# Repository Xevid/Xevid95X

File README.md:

# Xevid95X
 Xevid95X Keyboard for Junior Project

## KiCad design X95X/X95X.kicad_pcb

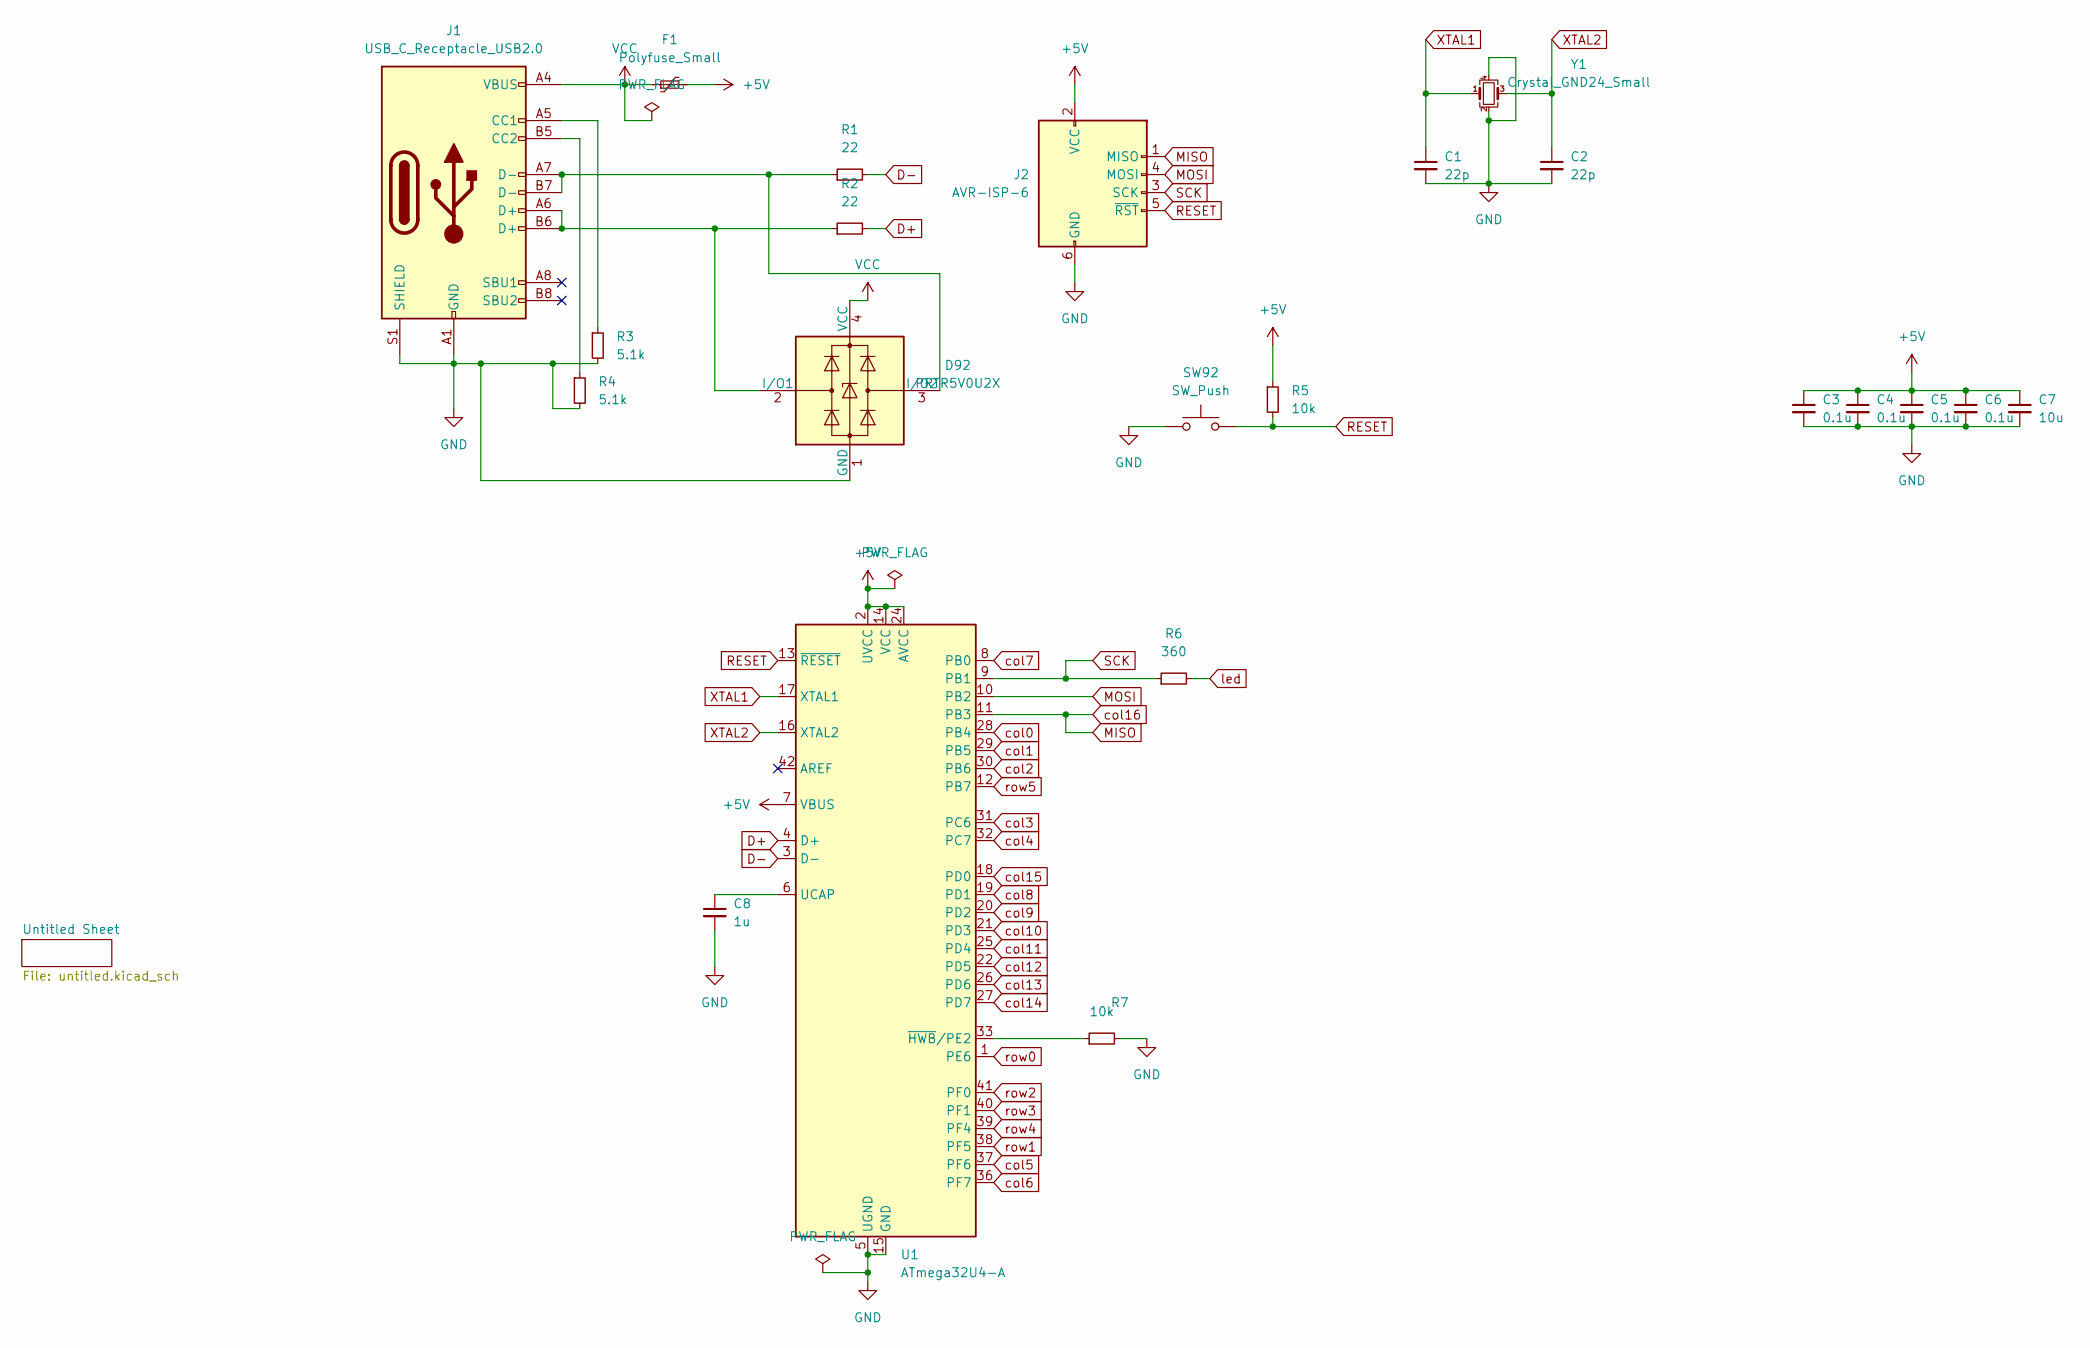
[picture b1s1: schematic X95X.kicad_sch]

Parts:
C1, C2: 22p; C_0805_2012Metric_Pad1.18x1.45mm_HandSolder
C3, C4, C5, C6: 0.1u; C_0805_2012Metric_Pad1.18x1.45mm_HandSolder
C7: 10u; C_0805_2012Metric_Pad1.18x1.45mm_HandSolder
C8: 1u; C_0805_2012Metric_Pad1.18x1.45mm_HandSolder
D92: PRTR5V0U2X; SOT143B
F1: Polyfuse_Small; Fuse_1206_3216Metric_Pad1.42x1.75mm_HandSolder
J1: USB_C_Receptacle_USB2.0; USB_C_Receptacle_HRO_TYPE-C-31-M-14
J2: AVR-ISP-6; Reset_Pretty-Mask
R1, R2: 22; R_0805_2012Metric_Pad1.20x1.40mm_HandSolder
R3, R4: 5.1k; R_0805_2012Metric_Pad1.20x1.40mm_HandSolder
R5, R7: 10k; R_0805_2012Metric_Pad1.20x1.40mm_HandSolder
R6: 360; R_0805_2012Metric_Pad1.20x1.40mm_HandSolder
SW92: SW_Push; SW_SPST_SKQG_WithStem
U1: ATmega32U4-A; TQFP-44_10x10mm_P0.8mm
Y1: Crystal_GND24_Small; Crystal_SMD_3225-4Pin_3.2x2.5mm_HandSoldering

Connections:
+5V: C3.1, C4.1, C5.1, C6.1, C7.1, F1.2, J2.2 (VCC), R5.1, U1.2 (UVCC), U1.7 (VBUS), U1.14 (VCC), U1.24 (AVCC), U1.34 (VCC), U1.44 (AVCC)
D+: R2.2, U1.4 (D+)
D-: R1.2, U1.3 (D-)
GND: C1.2, C2.2, C3.2, C4.2, C5.2, C6.2, C7.2, C8.2, D92.1 (GND), J1.A1 (GND), J1.A12 (GND), J1.B1 (GND), J1.B12 (GND), J1.S1 (SHIELD), J2.6 (GND), R3.2, R4.2, R7.2, SW92.1, U1.5 (UGND), U1.15 (GND), U1.23 (GND), U1.35 (GND), U1.43 (GND), Y1.2, Y1.4; also elsewhere on the board
MISO: J2.1 (MISO), U1.11 (PB3); also elsewhere on the board
MOSI: J2.4 (MOSI), U1.10 (PB2)
unnamed: C8.1, U1.6 (UCAP)
unnamed: D92.2 (I/O1), J1.A6 (D+), J1.B6 (D+), R2.1
unnamed: D92.3 (I/O2), J1.A7 (D-), J1.B7 (D-), R1.1
unnamed: J1.A5 (CC1), R3.1
unnamed: J1.B5 (CC2), R4.1
unnamed: R7.1, U1.33 (~HWB/PE2)
RESET: J2.5 (~RST), R5.2, SW92.2, U1.13 (~RESET)
SCK: J2.3 (SCK), R6.1, U1.9 (PB1)
VCC: D92.4 (VCC), F1.1, J1.A4 (VBUS), J1.A9 (VBUS), J1.B4 (VBUS), J1.B9 (VBUS); also elsewhere on the board
XTAL1: C1.1, U1.17 (XTAL1), Y1.1
XTAL2: C2.1, U1.16 (XTAL2), Y1.3
col0: U1.28 (PB4); also elsewhere on the board
col1: U1.29 (PB5); also elsewhere on the board
col2: U1.30 (PB6); also elsewhere on the board
col3: U1.31 (PC6); also elsewhere on the board
col4: U1.32 (PC7); also elsewhere on the board
col5: U1.37 (PF6); also elsewhere on the board
col6: U1.36 (PF7); also elsewhere on the board
col7: U1.8 (PB0); also elsewhere on the board
col8: U1.19 (PD1); also elsewhere on the board
col9: U1.20 (PD2); also elsewhere on the board
col10: U1.21 (PD3); also elsewhere on the board
col11: U1.25 (PD4); also elsewhere on the board
col12: U1.22 (PD5); also elsewhere on the board
col13: U1.26 (PD6); also elsewhere on the board
col14: U1.27 (PD7); also elsewhere on the board
col15: U1.18 (PD0); also elsewhere on the board
led: R6.2; also elsewhere on the board
row0: U1.1 (PE6); also elsewhere on the board
row1: U1.38 (PF5); also elsewhere on the board
row2: U1.41 (PF0); also elsewhere on the board
row3: U1.40 (PF1); also elsewhere on the board
row4: U1.39 (PF4); also elsewhere on the board
row5: U1.12 (PB7); also elsewhere on the board

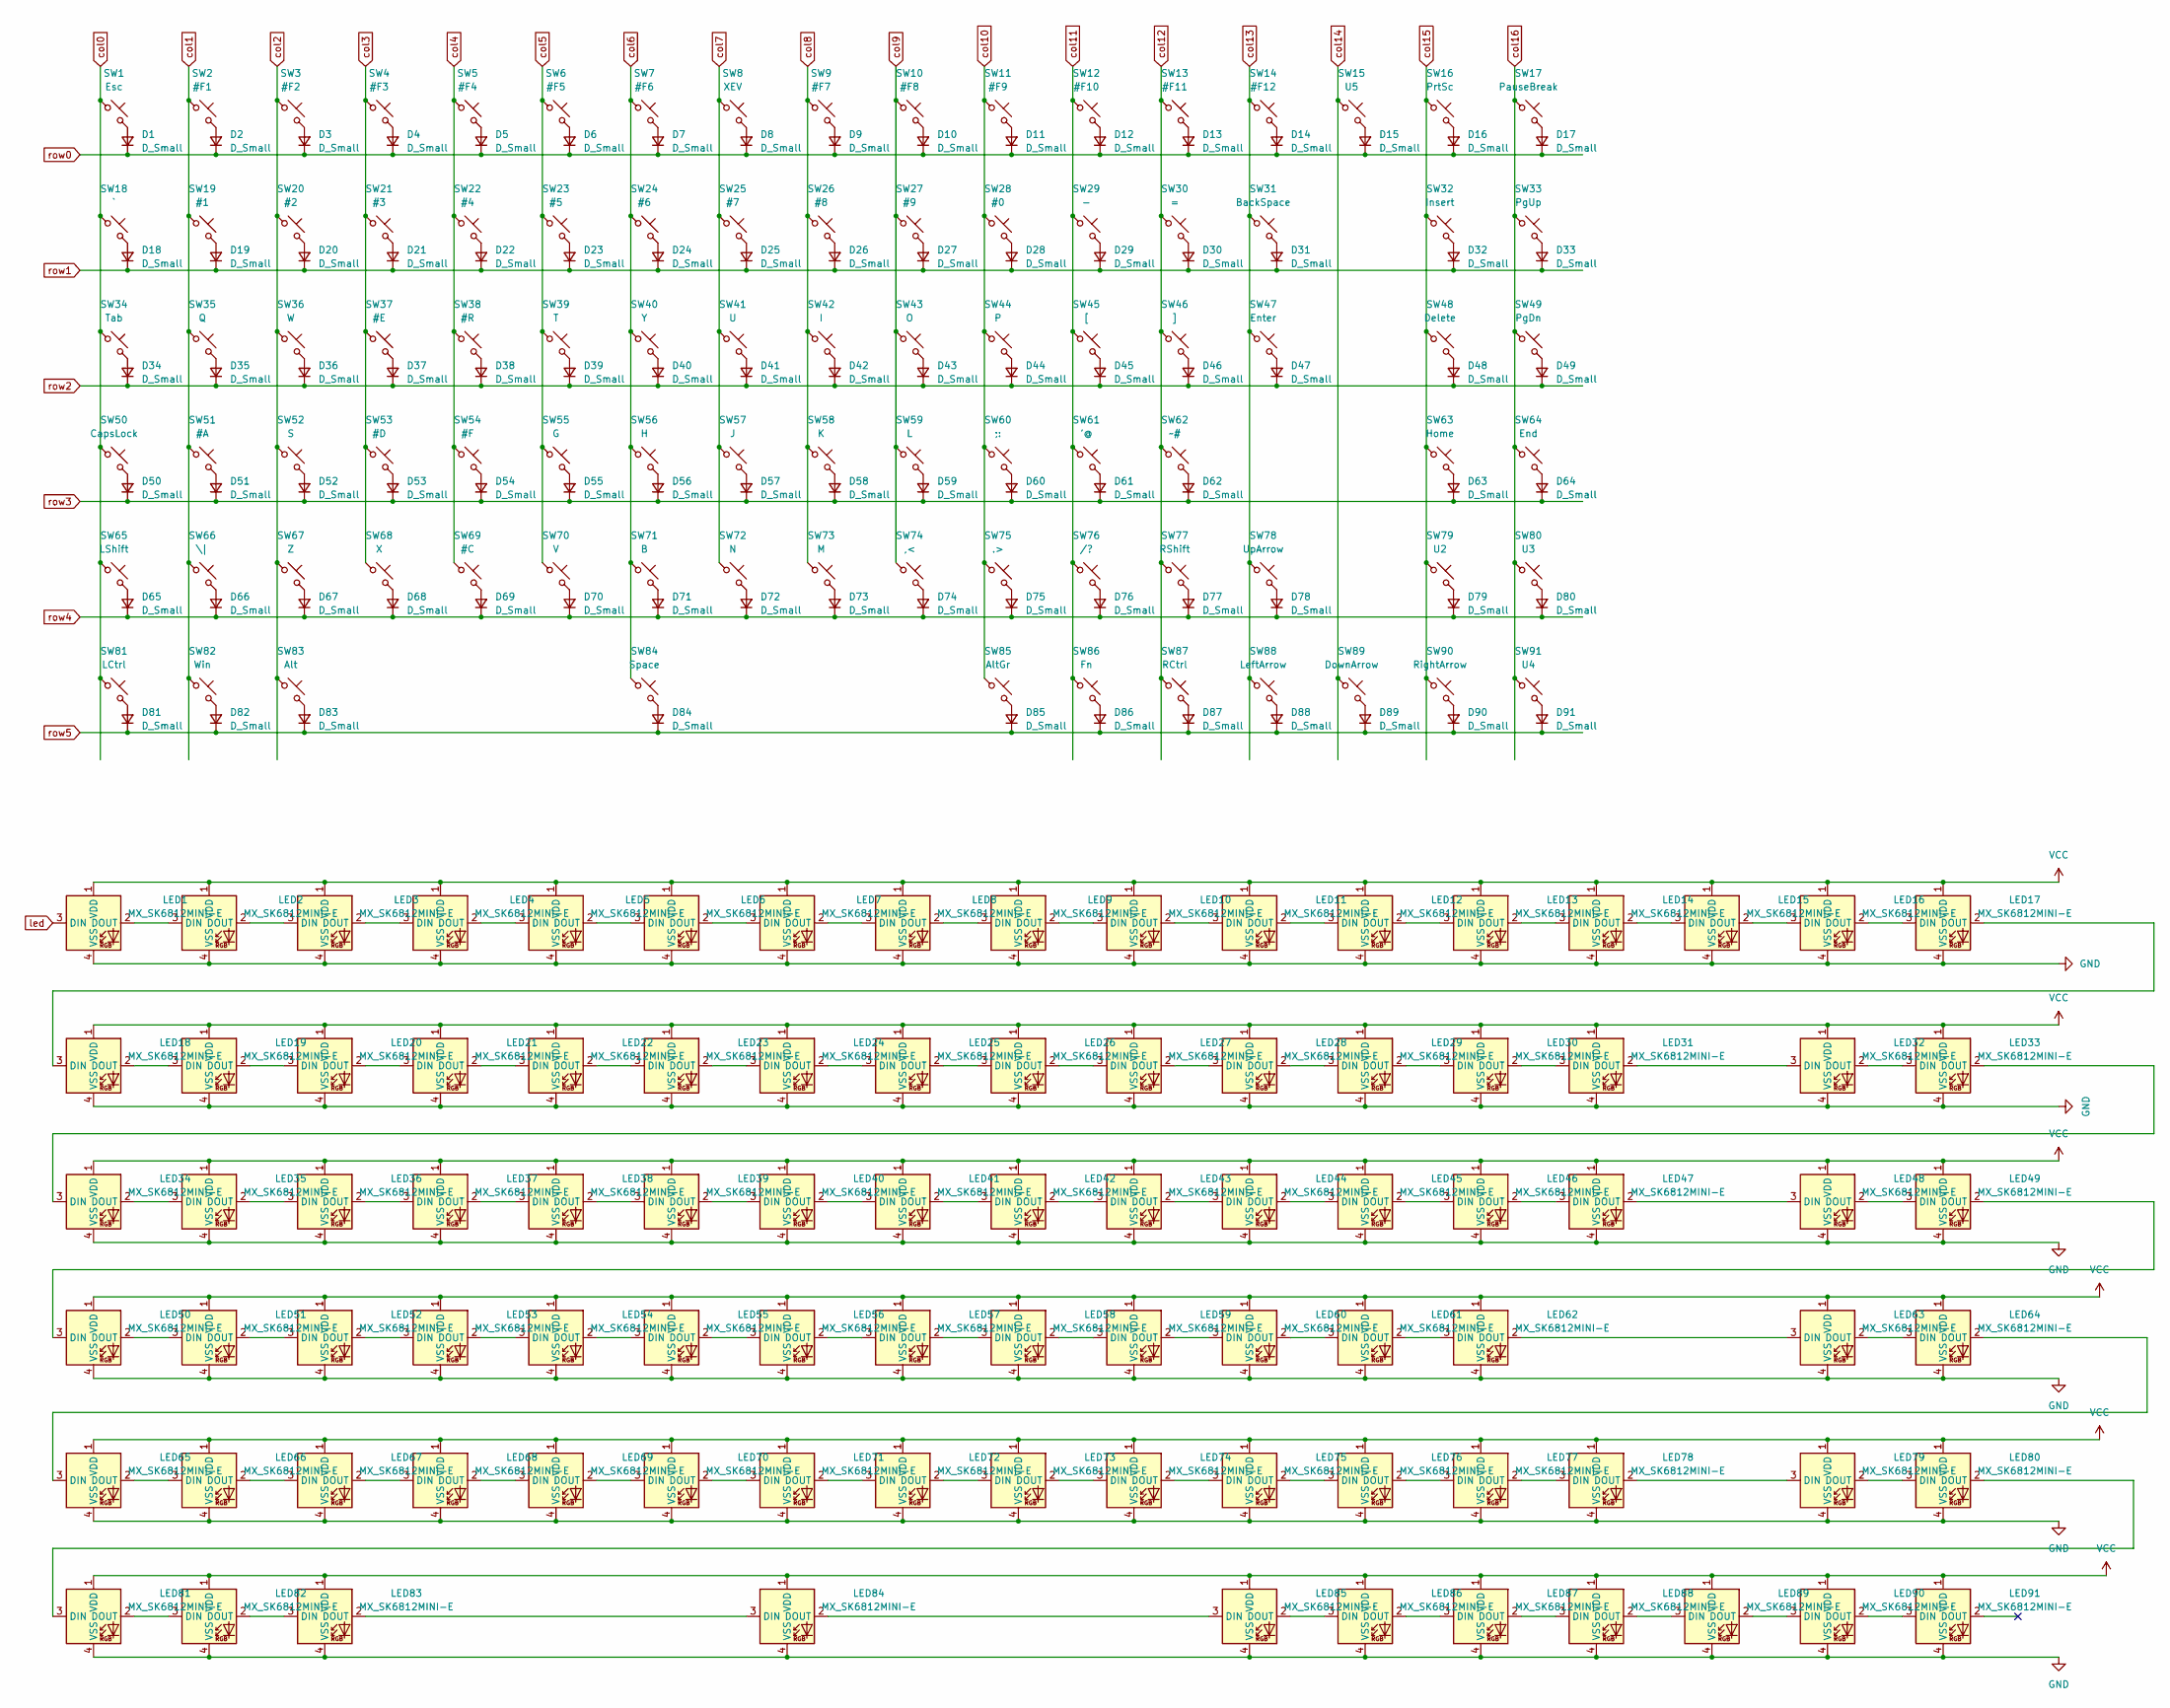
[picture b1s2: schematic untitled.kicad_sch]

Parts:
D1, D2, D3, D4, D5, D6, D7, D8, D9, D10, D11, D12, D13, D14, D15, D16, D17, D18, D19, D20, D21, D22, D23, D24, D25, D26, D27, D28, D29, D30, D31, D32, D33, D34, D35, D36, D37, D38, D39, D40, D41, D42, D43, D44, D45, D46, D47, D48, D49, D50, D51, D52, D53, D54, D55, D56, D57, D58, D59, D60, D61, D62, D63, D64, D65, D66, D67, D68, D69, D70, D71, D72, D73, D74, D75, D76, D77, D78, D79, D80, D81, D82, D83, D84, D85, D86, D87, D88, D89, D90, D91: D_Small; D_SOD-123
LED1, LED2, LED3, LED4, LED5, LED6, LED7, LED8, LED9, LED10, LED11, LED12, LED13, LED14, LED15, LED16, LED17, LED18, LED19, LED20, LED21, LED22, LED23, LED24, LED25, LED26, LED27, LED28, LED29, LED30, LED31, LED32, LED33, LED34, LED35, LED36, LED37, LED38, LED39, LED40, LED41, LED42, LED43, LED44, LED45, LED46, LED47, LED48, LED49, LED50, LED51, LED52, LED53, LED54, LED55, LED56, LED57, LED58, LED59, LED60, LED61, LED62, LED63, LED64, LED65, LED66, LED67, LED68, LED69, LED70, LED71, LED72, LED73, LED74, LED75, LED76, LED77, LED78, LED79, LED80, LED81, LED82, LED83, LED84, LED85, LED86, LED87, LED88, LED89, LED90, LED91: MX_SK6812MINI-E; LED_MX_6028R
SW1: Esc; SW_MX_1u
SW2: #F1; SW_MX_1u
SW3: #F2; SW_MX_1u
SW4: #F3; SW_MX_1u
SW5: #F4; SW_MX_1u
SW6: #F5; SW_MX_1u
SW7: #F6; SW_MX_1u
SW8: XEV; SW_MX_1u
SW9: #F7; SW_MX_1u
SW10: #F8; SW_MX_1u
SW11: #F9; SW_MX_1u
SW12: #F10; SW_MX_1u
SW13: #F11; SW_MX_1u
SW14: #F12; SW_MX_1u
SW15: U5; SW_MX_1u
SW16: PrtSc; SW_MX_1u
SW17: PauseBreak; SW_MX_1u
SW18: `; SW_MX_1u
SW19: #1; SW_MX_1u
SW20: #2; SW_MX_1u
SW21: #3; SW_MX_1u
SW22: #4; SW_MX_1u
SW23: #5; SW_MX_1u
SW24: #6; SW_MX_1u
SW25: #7; SW_MX_1u
SW26: #8; SW_MX_1u
SW27: #9; SW_MX_1u
SW28: #0; SW_MX_1u
SW29: -; SW_MX_1u
SW30: =; SW_MX_1u
SW31: BackSpace; SW_MX_1u
SW32: Insert; SW_MX_1u
SW33: PgUp; SW_MX_1u
SW34: Tab; SW_MX_1.5u
SW35: Q; SW_MX_1u
SW36: W; SW_MX_1u
SW37: #E; SW_MX_1u
SW38: #R; SW_MX_1u
SW39: T; SW_MX_1u
SW40: Y; SW_MX_1u
SW41: U; SW_MX_1u
SW42: I; SW_MX_1u
SW43: O; SW_MX_1u
SW44: P; SW_MX_1u
SW45: [; SW_MX_1u
SW46: ]; SW_MX_1u
SW47: Enter; SW_MX_1u
SW48: Delete; SW_MX_1u
SW49: PgDn; SW_MX_1u
SW50: CapsLock; SW_MX_1.75u
SW51: #A; SW_MX_1u
SW52: S; SW_MX_1u
SW53: #D; SW_MX_1u
SW54: #F; SW_MX_1u
SW55: G; SW_MX_1u
SW56: H; SW_MX_1u
SW57: J; SW_MX_1u
SW58: K; SW_MX_1u
SW59: L; SW_MX_1u
SW60: ;:; SW_MX_1u
SW61: '@; SW_MX_1u
SW62: ~#; SW_MX_1u
SW63: Home; SW_MX_1u
SW64: End; SW_MX_1u
SW65: LShift; SW_MX_1.25u
SW66: \|; SW_MX_1u
SW67: Z; SW_MX_1u
SW68: X; SW_MX_1u
SW69: #C; SW_MX_1u
SW70: V; SW_MX_1u
SW71: B; SW_MX_1u
SW72: N; SW_MX_1u
SW73: M; SW_MX_1u
SW74: ,<; SW_MX_1u
SW75: .>; SW_MX_1u
SW76: /?; SW_MX_1u
SW77: RShift; SW_MX_1.75u
SW78: UpArrow; SW_MX_1u
SW79: U2; SW_MX_1u
SW80: U3; SW_MX_1u
SW81: LCtrl; SW_MX_1.25u
SW82: Win; SW_MX_1.25u
SW83: Alt; SW_MX_1.25u
SW84: Space; SW_MX_1u
SW85: AltGr; SW_MX_1u
SW86: Fn; SW_MX_1u
SW87: RCtrl; SW_MX_1u
SW88: LeftArrow; SW_MX_1u
SW89: DownArrow; SW_MX_1u
SW90: RightArrow; SW_MX_1u
SW91: U4; SW_MX_1u

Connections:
GND: LED1.4 (VSS), LED2.4 (VSS), LED3.4 (VSS), LED4.4 (VSS), LED5.4 (VSS), LED6.4 (VSS), LED7.4 (VSS), LED8.4 (VSS), LED9.4 (VSS), LED10.4 (VSS), LED11.4 (VSS), LED12.4 (VSS), LED13.4 (VSS), LED14.4 (VSS), LED15.4 (VSS), LED16.4 (VSS), LED17.4 (VSS), LED18.4 (VSS), LED19.4 (VSS), LED20.4 (VSS), LED21.4 (VSS), LED22.4 (VSS), LED23.4 (VSS), LED24.4 (VSS), LED25.4 (VSS), LED26.4 (VSS), LED27.4 (VSS), LED28.4 (VSS), LED29.4 (VSS), LED30.4 (VSS), LED31.4 (VSS), LED32.4 (VSS), LED33.4 (VSS), LED34.4 (VSS), LED35.4 (VSS), LED36.4 (VSS), LED37.4 (VSS), LED38.4 (VSS), LED39.4 (VSS), LED40.4 (VSS), LED41.4 (VSS), LED42.4 (VSS), LED43.4 (VSS), LED44.4 (VSS), LED45.4 (VSS), LED46.4 (VSS), LED47.4 (VSS), LED48.4 (VSS), LED49.4 (VSS), LED50.4 (VSS), LED51.4 (VSS), LED52.4 (VSS), LED53.4 (VSS), LED54.4 (VSS), LED55.4 (VSS), LED56.4 (VSS), LED57.4 (VSS), LED58.4 (VSS), LED59.4 (VSS), LED60.4 (VSS), LED61.4 (VSS), LED62.4 (VSS), LED63.4 (VSS), LED64.4 (VSS), LED65.4 (VSS), LED66.4 (VSS), LED67.4 (VSS), LED68.4 (VSS), LED69.4 (VSS), LED70.4 (VSS), LED71.4 (VSS), LED72.4 (VSS), LED73.4 (VSS), LED74.4 (VSS), LED75.4 (VSS), LED76.4 (VSS), LED77.4 (VSS), LED78.4 (VSS), LED79.4 (VSS), LED80.4 (VSS), LED81.4 (VSS), LED82.4 (VSS), LED83.4 (VSS), LED84.4 (VSS), LED85.4 (VSS), LED86.4 (VSS), LED87.4 (VSS), LED88.4 (VSS), LED89.4 (VSS), LED90.4 (VSS), LED91.4 (VSS); also elsewhere on the board
MISO: SW17.1, SW33.1, SW49.1, SW64.1, SW80.1, SW91.1; also elsewhere on the board
unnamed: D1.2 (A), SW1.2
unnamed: D2.2 (A), SW2.2
unnamed: D3.2 (A), SW3.2
unnamed: D4.2 (A), SW4.2
unnamed: D5.2 (A), SW5.2
unnamed: D6.2 (A), SW6.2
unnamed: D7.2 (A), SW7.2
unnamed: D8.2 (A), SW8.2
unnamed: D9.2 (A), SW9.2
unnamed: D10.2 (A), SW10.2
unnamed: D11.2 (A), SW11.2
unnamed: D12.2 (A), SW12.2
unnamed: D13.2 (A), SW13.2
unnamed: D14.2 (A), SW14.2
unnamed: D15.2 (A), SW15.2
unnamed: D16.2 (A), SW16.2
unnamed: D17.2 (A), SW17.2
unnamed: D18.2 (A), SW18.2
unnamed: D19.2 (A), SW19.2
unnamed: D20.2 (A), SW20.2
unnamed: D21.2 (A), SW21.2
unnamed: D22.2 (A), SW22.2
unnamed: D23.2 (A), SW23.2
unnamed: D24.2 (A), SW24.2
unnamed: D25.2 (A), SW25.2
unnamed: D26.2 (A), SW26.2
unnamed: D27.2 (A), SW27.2
unnamed: D28.2 (A), SW28.2
unnamed: D29.2 (A), SW29.2
unnamed: D30.2 (A), SW30.2
unnamed: D31.2 (A), SW31.2
unnamed: D32.2 (A), SW32.2
unnamed: D33.2 (A), SW33.2
unnamed: D34.2 (A), SW34.2
unnamed: D35.2 (A), SW35.2
unnamed: D36.2 (A), SW36.2
unnamed: D37.2 (A), SW37.2
unnamed: D38.2 (A), SW38.2
unnamed: D39.2 (A), SW39.2
unnamed: D40.2 (A), SW40.2
unnamed: D41.2 (A), SW41.2
unnamed: D42.2 (A), SW42.2
unnamed: D43.2 (A), SW43.2
unnamed: D44.2 (A), SW44.2
unnamed: D45.2 (A), SW45.2
unnamed: D46.2 (A), SW46.2
unnamed: D47.2 (A), SW47.2
unnamed: D48.2 (A), SW48.2
unnamed: D49.2 (A), SW49.2
unnamed: D50.2 (A), SW50.2
unnamed: D51.2 (A), SW51.2
unnamed: D52.2 (A), SW52.2
unnamed: D53.2 (A), SW53.2
unnamed: D54.2 (A), SW54.2
unnamed: D55.2 (A), SW55.2
unnamed: D56.2 (A), SW56.2
unnamed: D57.2 (A), SW57.2
unnamed: D58.2 (A), SW58.2
unnamed: D59.2 (A), SW59.2
unnamed: D60.2 (A), SW60.2
unnamed: D61.2 (A), SW61.2
unnamed: D62.2 (A), SW62.2
unnamed: D63.2 (A), SW63.2
unnamed: D64.2 (A), SW64.2
unnamed: D65.2 (A), SW65.2
unnamed: D66.2 (A), SW66.2
unnamed: D67.2 (A), SW67.2
unnamed: D68.2 (A), SW68.2
unnamed: D69.2 (A), SW69.2
unnamed: D70.2 (A), SW70.2
unnamed: D71.2 (A), SW71.2
unnamed: D72.2 (A), SW72.2
unnamed: D73.2 (A), SW73.2
unnamed: D74.2 (A), SW74.2
unnamed: D75.2 (A), SW75.2
unnamed: D76.2 (A), SW76.2
unnamed: D77.2 (A), SW77.2
unnamed: D78.2 (A), SW78.2
unnamed: D79.2 (A), SW79.2
unnamed: D80.2 (A), SW80.2
unnamed: D81.2 (A), SW81.2
unnamed: D82.2 (A), SW82.2
unnamed: D83.2 (A), SW83.2
unnamed: D84.2 (A), SW84.2
unnamed: D85.2 (A), SW85.2
unnamed: D86.2 (A), SW86.2
unnamed: D87.2 (A), SW87.2
unnamed: D88.2 (A), SW88.2
unnamed: D89.2 (A), SW89.2
unnamed: D90.2 (A), SW90.2
unnamed: D91.2 (A), SW91.2
unnamed: LED1.2 (DOUT), LED2.3 (DIN)
unnamed: LED2.2 (DOUT), LED3.3 (DIN)
unnamed: LED3.2 (DOUT), LED4.3 (DIN)
unnamed: LED4.2 (DOUT), LED5.3 (DIN)
unnamed: LED5.2 (DOUT), LED6.3 (DIN)
unnamed: LED6.2 (DOUT), LED7.3 (DIN)
unnamed: LED7.2 (DOUT), LED8.3 (DIN)
unnamed: LED8.2 (DOUT), LED9.3 (DIN)
unnamed: LED10.2 (DOUT), LED11.3 (DIN)
unnamed: LED9.2 (DOUT), LED10.3 (DIN)
unnamed: LED11.2 (DOUT), LED12.3 (DIN)
unnamed: LED12.2 (DOUT), LED13.3 (DIN)
unnamed: LED13.2 (DOUT), LED14.3 (DIN)
unnamed: LED14.2 (DOUT), LED15.3 (DIN)
unnamed: LED15.2 (DOUT), LED16.3 (DIN)
unnamed: LED16.2 (DOUT), LED17.3 (DIN)
unnamed: LED17.2 (DOUT), LED18.3 (DIN)
unnamed: LED18.2 (DOUT), LED19.3 (DIN)
unnamed: LED19.2 (DOUT), LED20.3 (DIN)
unnamed: LED20.2 (DOUT), LED21.3 (DIN)
unnamed: LED21.2 (DOUT), LED22.3 (DIN)
unnamed: LED22.2 (DOUT), LED23.3 (DIN)
unnamed: LED23.2 (DOUT), LED24.3 (DIN)
unnamed: LED24.2 (DOUT), LED25.3 (DIN)
unnamed: LED25.2 (DOUT), LED26.3 (DIN)
unnamed: LED26.2 (DOUT), LED27.3 (DIN)
unnamed: LED27.2 (DOUT), LED28.3 (DIN)
unnamed: LED28.2 (DOUT), LED29.3 (DIN)
unnamed: LED29.2 (DOUT), LED30.3 (DIN)
unnamed: LED30.2 (DOUT), LED31.3 (DIN)
unnamed: LED32.2 (DOUT), LED33.3 (DIN)
unnamed: LED31.2 (DOUT), LED32.3 (DIN)
unnamed: LED33.2 (DOUT), LED34.3 (DIN)
unnamed: LED34.2 (DOUT), LED35.3 (DIN)
unnamed: LED35.2 (DOUT), LED36.3 (DIN)
unnamed: LED36.2 (DOUT), LED37.3 (DIN)
unnamed: LED37.2 (DOUT), LED38.3 (DIN)
unnamed: LED38.2 (DOUT), LED39.3 (DIN)
unnamed: LED39.2 (DOUT), LED40.3 (DIN)
unnamed: LED40.2 (DOUT), LED41.3 (DIN)
unnamed: LED41.2 (DOUT), LED42.3 (DIN)
unnamed: LED42.2 (DOUT), LED43.3 (DIN)
unnamed: LED43.2 (DOUT), LED44.3 (DIN)
unnamed: LED44.2 (DOUT), LED45.3 (DIN)
unnamed: LED45.2 (DOUT), LED46.3 (DIN)
unnamed: LED46.2 (DOUT), LED47.3 (DIN)
unnamed: LED48.2 (DOUT), LED49.3 (DIN)
unnamed: LED47.2 (DOUT), LED48.3 (DIN)
unnamed: LED49.2 (DOUT), LED50.3 (DIN)
unnamed: LED50.2 (DOUT), LED51.3 (DIN)
unnamed: LED51.2 (DOUT), LED52.3 (DIN)
unnamed: LED52.2 (DOUT), LED53.3 (DIN)
unnamed: LED53.2 (DOUT), LED54.3 (DIN)
unnamed: LED54.2 (DOUT), LED55.3 (DIN)
unnamed: LED55.2 (DOUT), LED56.3 (DIN)
unnamed: LED56.2 (DOUT), LED57.3 (DIN)
unnamed: LED57.2 (DOUT), LED58.3 (DIN)
unnamed: LED58.2 (DOUT), LED59.3 (DIN)
unnamed: LED59.2 (DOUT), LED60.3 (DIN)
unnamed: LED60.2 (DOUT), LED61.3 (DIN)
unnamed: LED61.2 (DOUT), LED62.3 (DIN)
unnamed: LED62.2 (DOUT), LED63.3 (DIN)
unnamed: LED63.2 (DOUT), LED64.3 (DIN)
unnamed: LED64.2 (DOUT), LED65.3 (DIN)
unnamed: LED65.2 (DOUT), LED66.3 (DIN)
unnamed: LED66.2 (DOUT), LED67.3 (DIN)
unnamed: LED67.2 (DOUT), LED68.3 (DIN)
unnamed: LED68.2 (DOUT), LED69.3 (DIN)
unnamed: LED69.2 (DOUT), LED70.3 (DIN)
unnamed: LED70.2 (DOUT), LED71.3 (DIN)
unnamed: LED71.2 (DOUT), LED72.3 (DIN)
unnamed: LED72.2 (DOUT), LED73.3 (DIN)
unnamed: LED73.2 (DOUT), LED74.3 (DIN)
unnamed: LED74.2 (DOUT), LED75.3 (DIN)
unnamed: LED75.2 (DOUT), LED76.3 (DIN)
unnamed: LED76.2 (DOUT), LED77.3 (DIN)
unnamed: LED77.2 (DOUT), LED78.3 (DIN)
unnamed: LED78.2 (DOUT), LED79.3 (DIN)
unnamed: LED79.2 (DOUT), LED80.3 (DIN)
unnamed: LED80.2 (DOUT), LED81.3 (DIN)
unnamed: LED81.2 (DOUT), LED82.3 (DIN)
unnamed: LED82.2 (DOUT), LED83.3 (DIN)
unnamed: LED83.2 (DOUT), LED84.3 (DIN)
unnamed: LED84.2 (DOUT), LED85.3 (DIN)
unnamed: LED86.2 (DOUT), LED87.3 (DIN)
unnamed: LED85.2 (DOUT), LED86.3 (DIN)
unnamed: LED87.2 (DOUT), LED88.3 (DIN)
unnamed: LED89.2 (DOUT), LED90.3 (DIN)
unnamed: LED88.2 (DOUT), LED89.3 (DIN)
unnamed: LED90.2 (DOUT), LED91.3 (DIN)
VCC: LED1.1 (VDD), LED2.1 (VDD), LED3.1 (VDD), LED4.1 (VDD), LED5.1 (VDD), LED6.1 (VDD), LED7.1 (VDD), LED8.1 (VDD), LED9.1 (VDD), LED10.1 (VDD), LED11.1 (VDD), LED12.1 (VDD), LED13.1 (VDD), LED14.1 (VDD), LED15.1 (VDD), LED16.1 (VDD), LED17.1 (VDD), LED18.1 (VDD), LED19.1 (VDD), LED20.1 (VDD), LED21.1 (VDD), LED22.1 (VDD), LED23.1 (VDD), LED24.1 (VDD), LED25.1 (VDD), LED26.1 (VDD), LED27.1 (VDD), LED28.1 (VDD), LED29.1 (VDD), LED30.1 (VDD), LED31.1 (VDD), LED32.1 (VDD), LED33.1 (VDD), LED34.1 (VDD), LED35.1 (VDD), LED36.1 (VDD), LED37.1 (VDD), LED38.1 (VDD), LED39.1 (VDD), LED40.1 (VDD), LED41.1 (VDD), LED42.1 (VDD), LED43.1 (VDD), LED44.1 (VDD), LED45.1 (VDD), LED46.1 (VDD), LED47.1 (VDD), LED48.1 (VDD), LED49.1 (VDD), LED50.1 (VDD), LED51.1 (VDD), LED52.1 (VDD), LED53.1 (VDD), LED54.1 (VDD), LED55.1 (VDD), LED56.1 (VDD), LED57.1 (VDD), LED58.1 (VDD), LED59.1 (VDD), LED60.1 (VDD), LED61.1 (VDD), LED62.1 (VDD), LED63.1 (VDD), LED64.1 (VDD), LED65.1 (VDD), LED66.1 (VDD), LED67.1 (VDD), LED68.1 (VDD), LED69.1 (VDD), LED70.1 (VDD), LED71.1 (VDD), LED72.1 (VDD), LED73.1 (VDD), LED74.1 (VDD), LED75.1 (VDD), LED76.1 (VDD), LED77.1 (VDD), LED78.1 (VDD), LED79.1 (VDD), LED80.1 (VDD), LED81.1 (VDD), LED82.1 (VDD), LED83.1 (VDD), LED84.1 (VDD), LED85.1 (VDD), LED86.1 (VDD), LED87.1 (VDD), LED88.1 (VDD), LED89.1 (VDD), LED90.1 (VDD), LED91.1 (VDD); also elsewhere on the board
col0: SW1.1, SW18.1, SW34.1, SW50.1, SW65.1, SW81.1; also elsewhere on the board
col1: SW2.1, SW19.1, SW35.1, SW51.1, SW66.1, SW82.1; also elsewhere on the board
col2: SW3.1, SW20.1, SW36.1, SW52.1, SW67.1, SW83.1; also elsewhere on the board
col3: SW4.1, SW21.1, SW37.1, SW53.1, SW68.1; also elsewhere on the board
col4: SW5.1, SW22.1, SW38.1, SW54.1, SW69.1; also elsewhere on the board
col5: SW6.1, SW23.1, SW39.1, SW55.1, SW70.1; also elsewhere on the board
col6: SW7.1, SW24.1, SW40.1, SW56.1, SW71.1, SW84.1; also elsewhere on the board
col7: SW8.1, SW25.1, SW41.1, SW57.1, SW72.1; also elsewhere on the board
col8: SW9.1, SW26.1, SW42.1, SW58.1, SW73.1; also elsewhere on the board
col9: SW10.1, SW27.1, SW43.1, SW59.1, SW74.1; also elsewhere on the board
col10: SW11.1, SW28.1, SW44.1, SW60.1, SW75.1, SW85.1; also elsewhere on the board
col11: SW12.1, SW29.1, SW45.1, SW61.1, SW76.1, SW86.1; also elsewhere on the board
col12: SW13.1, SW30.1, SW46.1, SW62.1, SW77.1, SW87.1; also elsewhere on the board
col13: SW14.1, SW31.1, SW47.1, SW78.1, SW88.1; also elsewhere on the board
col14: SW15.1, SW89.1; also elsewhere on the board
col15: SW16.1, SW32.1, SW48.1, SW63.1, SW79.1, SW90.1; also elsewhere on the board
led: LED1.3 (DIN); also elsewhere on the board
row0: D1.1 (K), D2.1 (K), D3.1 (K), D4.1 (K), D5.1 (K), D6.1 (K), D7.1 (K), D8.1 (K), D9.1 (K), D10.1 (K), D11.1 (K), D12.1 (K), D13.1 (K), D14.1 (K), D15.1 (K), D16.1 (K), D17.1 (K); also elsewhere on the board
row1: D18.1 (K), D19.1 (K), D20.1 (K), D21.1 (K), D22.1 (K), D23.1 (K), D24.1 (K), D25.1 (K), D26.1 (K), D27.1 (K), D28.1 (K), D29.1 (K), D30.1 (K), D31.1 (K), D32.1 (K), D33.1 (K); also elsewhere on the board
row2: D34.1 (K), D35.1 (K), D36.1 (K), D37.1 (K), D38.1 (K), D39.1 (K), D40.1 (K), D41.1 (K), D42.1 (K), D43.1 (K), D44.1 (K), D45.1 (K), D46.1 (K), D47.1 (K), D48.1 (K), D49.1 (K); also elsewhere on the board
row3: D50.1 (K), D51.1 (K), D52.1 (K), D53.1 (K), D54.1 (K), D55.1 (K), D56.1 (K), D57.1 (K), D58.1 (K), D59.1 (K), D60.1 (K), D61.1 (K), D62.1 (K), D63.1 (K), D64.1 (K); also elsewhere on the board
row4: D65.1 (K), D66.1 (K), D67.1 (K), D68.1 (K), D69.1 (K), D70.1 (K), D71.1 (K), D72.1 (K), D73.1 (K), D74.1 (K), D75.1 (K), D76.1 (K), D77.1 (K), D78.1 (K), D79.1 (K), D80.1 (K); also elsewhere on the board
row5: D81.1 (K), D82.1 (K), D83.1 (K), D84.1 (K), D85.1 (K), D86.1 (K), D87.1 (K), D88.1 (K), D89.1 (K), D90.1 (K), D91.1 (K); also elsewhere on the board

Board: 2 copper layers, 295 parts (204 on the bottom side), 221 nets, no tracks yet.

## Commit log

2022-11-13 Add submodules
2022-11-13 v1
    This time we have an actual description:
    keyboard has a USB-C connector currently being developed and a last resort 6 pin board. Removed key switches. (WILL BE BACK, just in a different way)
2022-11-14 v1a
    USB-C connector finished, refining circuitry.
2022-11-14 v1a1
    Redid reset switch. Next phase is the keyboard switch matrix. Yay.
2022-11-14 v1a2.0
    Preparation for switch matrix.
2022-11-14 v1a2.0b
    More switch matrix prep!
2022-11-14 v1b
    Main notes -
    Switch matrix added however not finished.
    Minor notes -
    Backspace is the only modified key to have been created so far.
2022-11-15 v1b2.2
    Finished basic switch matrix layout.
2022-11-15 v1b2.4
    More switch matrix crap. Also we hit 5000+ lines of code.
2022-11-15 v1b2.6
    Switch matrix annotated.
2022-11-15 v1b2.7
    more matrix stuff
2022-11-16 v1b3
    who knows at this point, let's be real it was kicad doing a funny
2022-11-17 v1c
    Redid switch matrix for like 3rd time?
2022-11-17 v1d
    :skull: you do not want to know.
2022-11-18 v1c2
    Redid switch matrix, AGAIN.
2022-11-22 v.1a
    Redoing the whole thing, again!
2022-12-11 v.15c
2022-12-12 v.6c
2022-12-13 v.7c
2022-12-14 v1xa
2022-12-14 v1za
2022-12-14 v1zac
2022-12-14 PCB!!!
2022-12-14 more pcb
